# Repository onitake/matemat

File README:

Matemat
=======

The Matemat is a vending machine for carbonated soft drinks.
All hardware and software was designed by members of
(Chaostreff Basel)[1] and released in the form of circuit
diagrams, printed circuit board layouts and source code
for anyone to use and modify.

Under certain restrictions, even commercial exploitation is
permissible. Please see the accompanying LICENSE file for
details.

The name "Matemat" is a portmanteau of "mate" (as in mate
tea) and "automat" (the German word for vending machine).

The device is mainly intended to dispense mate tea based
soft drinks, but may be used for other types of beverages
too.

To build the first prototype, an old vending machine with
a cooled bottle compartment was repurposed.

The software source code can be (downloaded separately)[2].

[1] http://www.chaostreff.ch
[2] https://github.com/onitake/matecontrol

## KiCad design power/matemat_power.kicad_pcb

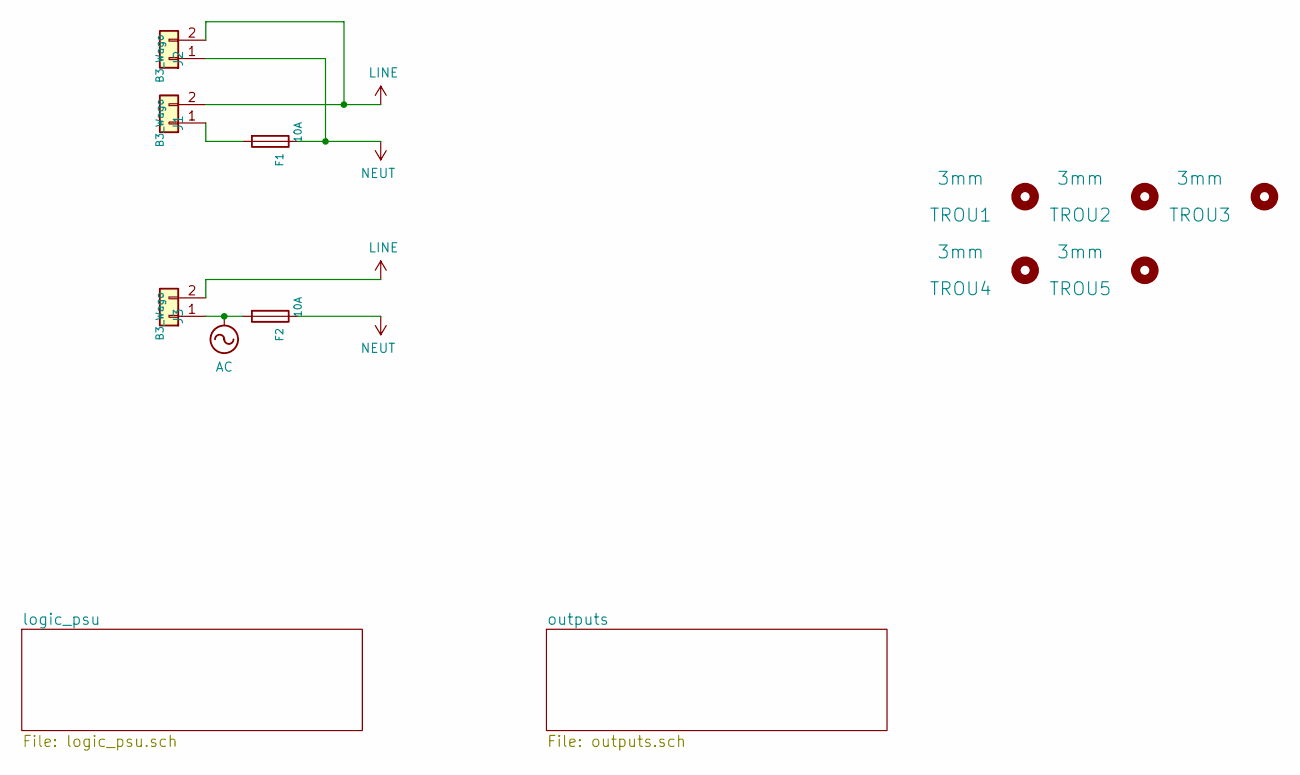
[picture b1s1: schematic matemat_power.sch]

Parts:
F1, F2: 10A; Fuseholder_Cylinder-5x20mm_Schurter_0031_8201_Horizontal_Op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
J1, J2, J3: B3_Wago; TerminalBlock_WAGO_236-402_1x02_P5.00mm_45Degree
TROU1, TROU2, TROU3, TROU4, TROU5: 3mm; MountingHole_3.2mm_M3

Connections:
AC: F2.2, J3.1; also elsewhere on the board
LINE: J1.2, J2.2, J3.2; also elsewhere on the board
NEUT: F1.1, F2.1, J2.1; also elsewhere on the board
unnamed: F1.2, J1.1

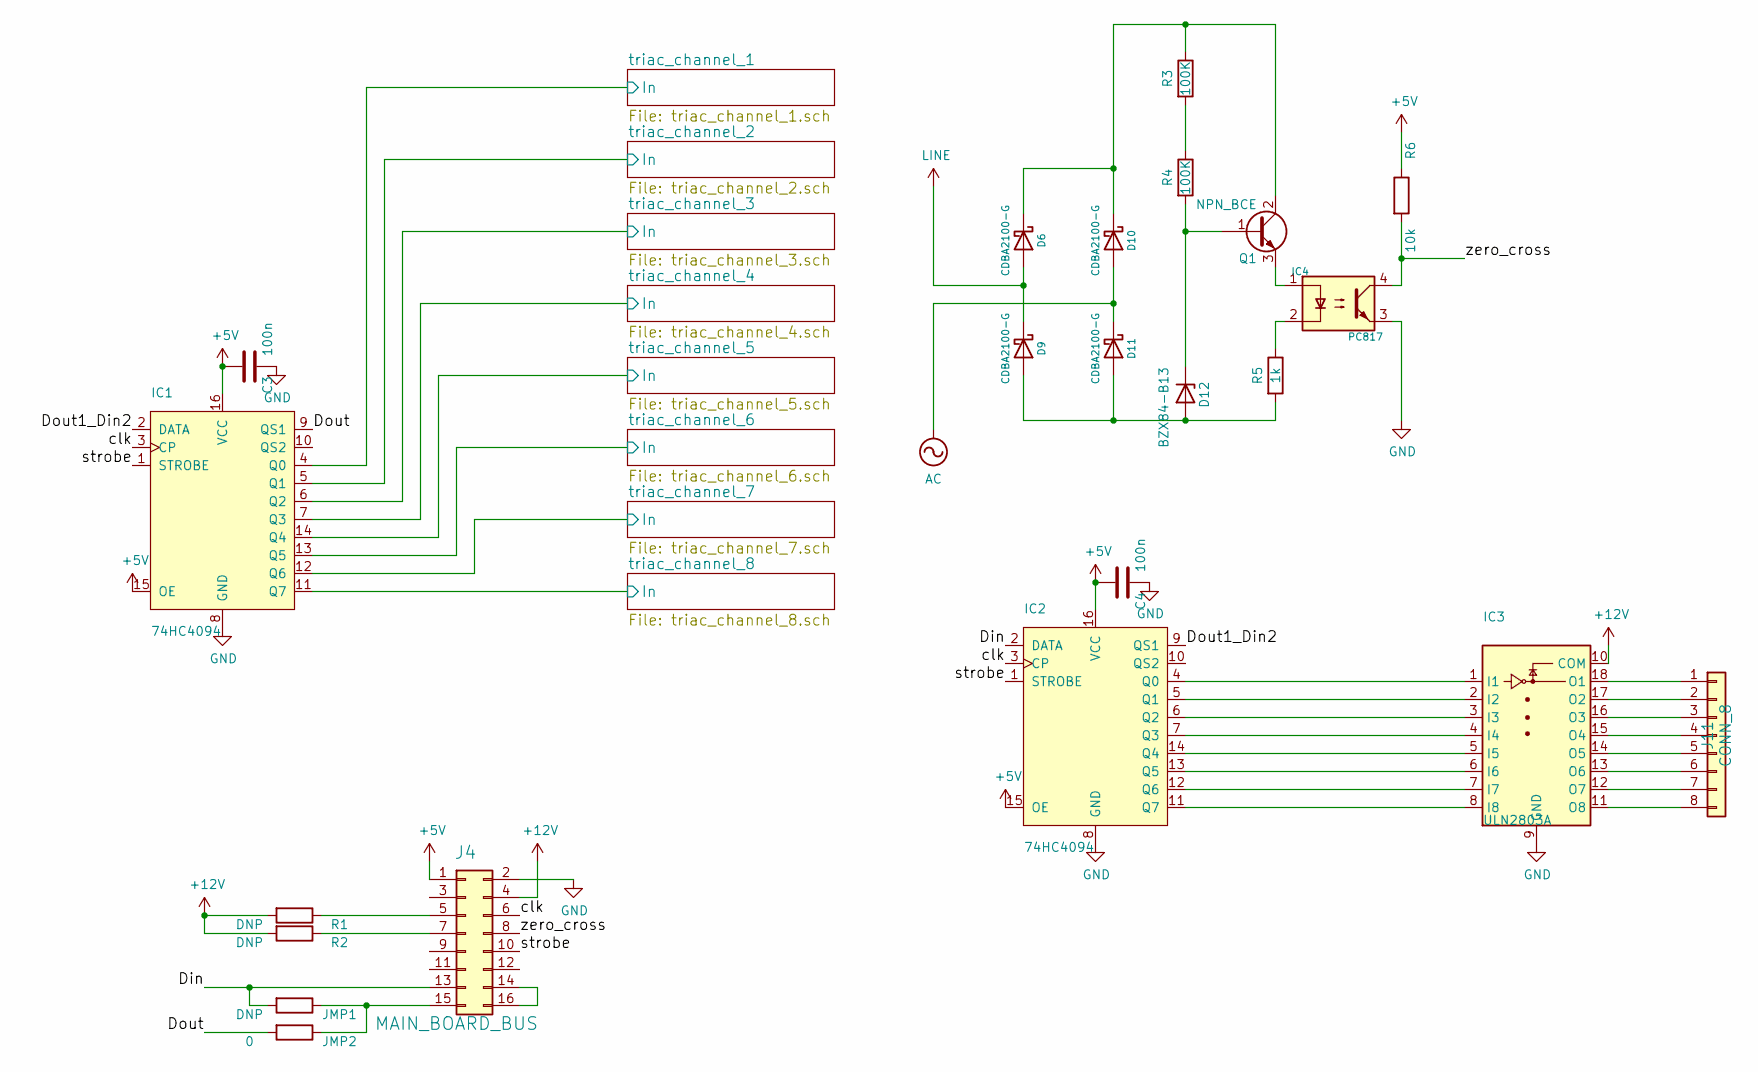
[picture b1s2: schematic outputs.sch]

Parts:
C3, C4: 100n; C_0805_2012Metric_Pad1.18x1.45mm_HandSolder
D6, D9, D10, D11: CDBA2100-G; D_SMA
D12: BZX84-B13; D_SOT-23_ANK
IC1, IC2: 74HC4094; SOIC-16_3.9x9.9mm_P1.27mm
IC3: ULN2803A; SOIC-18W_7.5x11.6mm_P1.27mm
IC4: PC817; DIP-4_W7.62mm
J4: MAIN_BOARD_BUS; PinHeader_2x08_P2.54mm_Vertical
J11: CONN_8; TerminalBlock_Phoenix_MPT-0,5-8-2.54_1x08_P2.54mm_Horizontal
JMP1: DNP; R_0603_1608Metric_Pad0.98x0.95mm_HandSolder
JMP2: 0; R_0603_1608Metric_Pad0.98x0.95mm_HandSolder
Q1: NPN_BCE; TO-220-3_Vertical
R1, R2: DNP; R_0603_1608Metric_Pad0.98x0.95mm_HandSolder
R3, R4: 100K; R_Axial_DIN0309_L9.0mm_D3.2mm_P12.70mm_Horizontal
R5: 1k; R_0805_2012Metric_Pad1.20x1.40mm_HandSolder
R6: 10k; R_0805_2012Metric_Pad1.20x1.40mm_HandSolder

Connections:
+5V: C3.2, C4.2, IC1.15 (OE), IC1.16 (VCC), IC2.15 (OE), IC2.16 (VCC), J4.1, R6.1
+12V: IC3.10 (COM), J4.4, R1.2, R2.2; also elsewhere on the board
/outputs/Din: IC2.2 (DATA), J4.13, JMP1.2
/outputs/Dout: IC1.9 (QS1), JMP2.2
/outputs/Dout1_Din2: IC1.2 (DATA), IC2.9 (QS1)
/outputs/clk: IC1.3 (CP), IC2.3 (CP), J4.6
/outputs/strobe: IC1.1 (STROBE), IC2.1 (STROBE), J4.10
/outputs/triac_channel_1/In: IC1.4 (Q0); also elsewhere on the board
/outputs/triac_channel_2/In: IC1.5 (Q1); also elsewhere on the board
/outputs/triac_channel_3/In: IC1.6 (Q2); also elsewhere on the board
/outputs/triac_channel_4/In: IC1.7 (Q3); also elsewhere on the board
/outputs/triac_channel_5/In: IC1.14 (Q4); also elsewhere on the board
/outputs/triac_channel_6/In: IC1.13 (Q5); also elsewhere on the board
/outputs/triac_channel_7/In: IC1.12 (Q6); also elsewhere on the board
/outputs/triac_channel_8/In: IC1.11 (Q7); also elsewhere on the board
/outputs/zero_cross: IC4.4, J4.8, R6.2
AC: D10.2 (A), D11.1 (K); also elsewhere on the board
GND: C3.1, C4.1, IC1.8 (GND), IC2.8 (GND), IC3.9 (GND), IC4.3, J4.2; also elsewhere on the board
LINE: D6.2 (A), D9.1 (K); also elsewhere on the board
unnamed: D6.1 (K), D10.1 (K), Q1.2 (C), R3.1
unnamed: D9.2 (A), D11.2 (A), D12.2 (A), R5.2
unnamed: D12.1 (K), Q1.1 (B), R4.2
unnamed: IC2.4 (Q0), IC3.1 (I1)
unnamed: IC2.5 (Q1), IC3.2 (I2)
unnamed: IC2.6 (Q2), IC3.3 (I3)
unnamed: IC2.7 (Q3), IC3.4 (I4)
unnamed: IC2.11 (Q7), IC3.8 (I8)
unnamed: IC2.12 (Q6), IC3.7 (I7)
unnamed: IC2.13 (Q5), IC3.6 (I6)
unnamed: IC2.14 (Q4), IC3.5 (I5)
unnamed: IC3.11 (O8), J11.8
unnamed: IC3.12 (O7), J11.7
unnamed: IC3.13 (O6), J11.6
unnamed: IC3.14 (O5), J11.5
unnamed: IC3.15 (O4), J11.4
unnamed: IC3.16 (O3), J11.3
unnamed: IC3.17 (O2), J11.2
unnamed: IC3.18 (O1), J11.1
unnamed: IC4.1, Q1.3 (E)
unnamed: IC4.2, R5.1
unnamed: J4.5, R1.1
unnamed: J4.7, R2.1
unnamed: J4.14, J4.16
unnamed: J4.15, JMP1.1, JMP2.1
unnamed: R3.2, R4.1

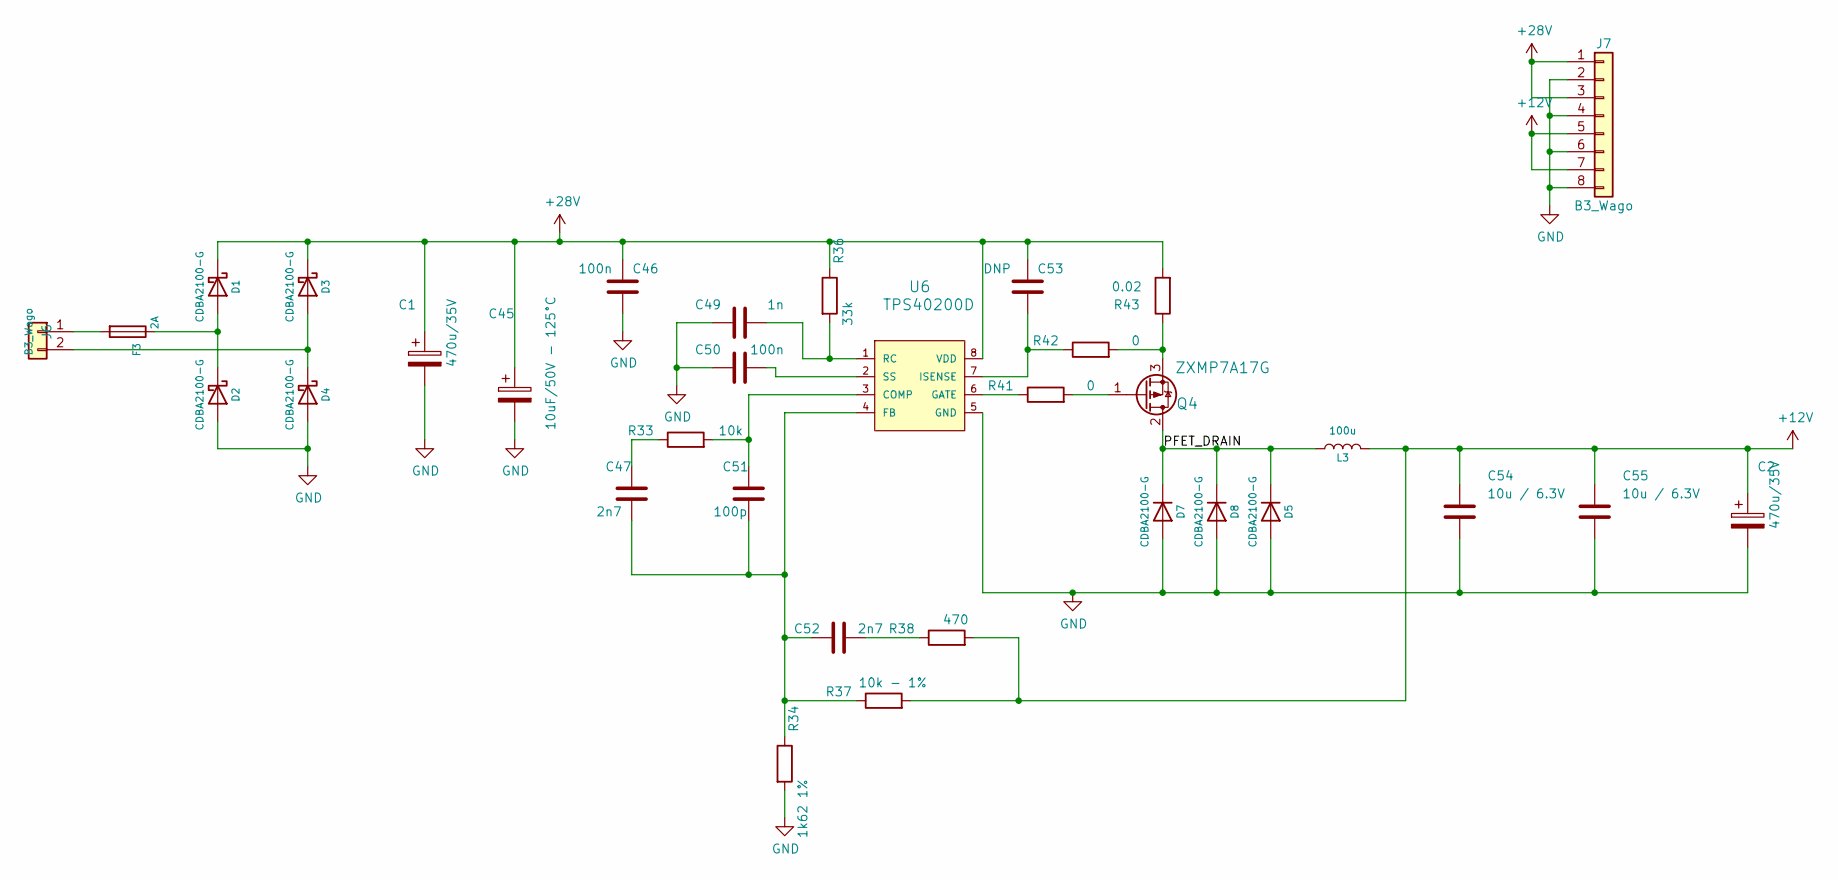
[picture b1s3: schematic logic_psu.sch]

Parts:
C1, C2: 470u/35V; CP_Radial_D10.0mm_P5.00mm
C45: 10uF/50V - 125°C; CP_Radial_D10.0mm_P5.00mm
C46, C50: 100n; C_0805_2012Metric_Pad1.18x1.45mm_HandSolder
C47, C52: 2n7; C_0805_2012Metric_Pad1.18x1.45mm_HandSolder
C49: 1n; C_0805_2012Metric_Pad1.18x1.45mm_HandSolder
C51: 100p; C_0805_2012Metric_Pad1.18x1.45mm_HandSolder
C53: DNP; C_0805_2012Metric_Pad1.18x1.45mm_HandSolder
C54, C55: 10u / 6.3V; C_0805_2012Metric_Pad1.18x1.45mm_HandSolder
D1, D2, D3, D4, D5, D7, D8: CDBA2100-G; D_SMA
F3: 2A; Fuseholder_Cylinder-5x20mm_Schurter_0031_8201_Horizontal_Op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
J6: B3_Wago; TerminalBlock_WAGO_236-402_1x02_P5.00mm_45Degree
J7: B3_Wago; TerminalBlock_WAGO_236-408_1x08_P5.00mm_45Degree
L3: 100u; L_Toroid_Vertical_L22.4mm_W10.2mm_P7.90mm_Vishay_TJ4
Q4: ZXMP7A17G; SOT-223-3_TabPin2
R33: 10k; R_0805_2012Metric_Pad1.20x1.40mm_HandSolder
R34: 1k62 1%; R_0805_2012Metric_Pad1.20x1.40mm_HandSolder
R36: 33k; R_0805_2012Metric_Pad1.20x1.40mm_HandSolder
R37: 10k - 1%; R_0805_2012Metric_Pad1.20x1.40mm_HandSolder
R38: 470; R_0805_2012Metric_Pad1.20x1.40mm_HandSolder
R41, R42: 0; R_0805_2012Metric_Pad1.20x1.40mm_HandSolder
R43: 0.02; R_2010_5025Metric_Pad1.40x2.65mm_HandSolder
U6: TPS40200D; SOIC-8_3.9x4.9mm_P1.27mm

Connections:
+12V: C2.1, C54.1, C55.1, J7.5, J7.7, L3.2, R37.2, R38.2; also elsewhere on the board
+28V: C1.1, C45.1, C46.1, C53.1, D1.1 (K), D3.1 (K), J7.1, J7.3, R36.1, R43.2, U6.8 (VDD)
/logic_psu/PFET_DRAIN: D5.1 (K), D7.1 (K), D8.1 (K), L3.1, Q4.2 (D)
GND: C1.2, C2.2, C45.2, C46.2, C49.1, C50.1, C54.2, C55.2, D2.2 (A), D4.2 (A), D5.2 (A), D7.2 (A), D8.2 (A), J7.2, J7.4, J7.6, J7.8, R34.2, U6.5 (GND); also elsewhere on the board
unnamed: C47.1, R33.1
unnamed: C47.2, C51.2, C52.1, R34.1, R37.1, U6.4 (FB)
unnamed: C49.2, R36.2, U6.1 (RC)
unnamed: C50.2, U6.2 (SS)
unnamed: C51.1, R33.2, U6.3 (COMP)
unnamed: C52.2, R38.1
unnamed: C53.2, R42.1, U6.7 (ISENSE)
unnamed: D1.2 (A), D2.1 (K), F3.1
unnamed: D3.2 (A), D4.1 (K), J6.2
unnamed: F3.2, J6.1
unnamed: Q4.1 (G), R41.2
unnamed: Q4.3 (S), R42.2, R43.1
unnamed: R41.1, U6.6 (GATE)

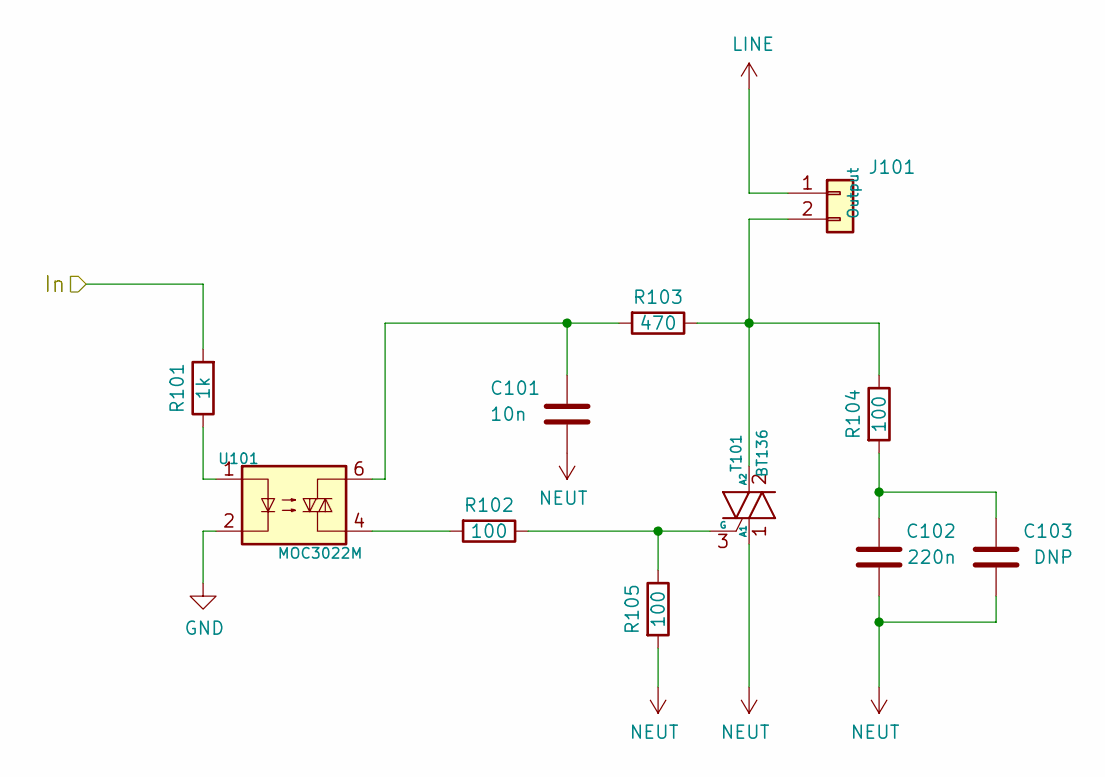
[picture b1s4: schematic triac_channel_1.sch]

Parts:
C101: 10n; C_Rect_L7.0mm_W2.5mm_P5.00mm
C102: 220n; C_Rect_L18.0mm_W5.0mm_P15.00mm_FKS3_FKP3
C103: DNP; C_Rect_L13.0mm_W4.0mm_P10.00mm_FKS3_FKP3_MKS4
J101: Output; TerminalBlock_WAGO_236-402_1x02_P5.00mm_45Degree
R101: 1k; R_0805_2012Metric_Pad1.20x1.40mm_HandSolder
R102, R104: 100; R_Axial_DIN0309_L9.0mm_D3.2mm_P12.70mm_Horizontal
R103: 470; R_Axial_DIN0309_L9.0mm_D3.2mm_P12.70mm_Horizontal
R105: 100; R_0805_2012Metric_Pad1.20x1.40mm_HandSolder
T101: BT136; TO-220-3_Vertical
U101: MOC3022M; DIP-6_W7.62mm_LongPads

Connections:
/outputs/triac_channel_1/In: R101.2; also elsewhere on the board
GND: U101.2; also elsewhere on the board
LINE: J101.1; also elsewhere on the board
NEUT: C101.2, C102.2, C103.2, R105.2, T101.1 (A1); also elsewhere on the board
unnamed: C101.1, R103.2, U101.6
unnamed: C102.1, C103.1, R104.2
unnamed: J101.2, R103.1, R104.1, T101.2 (A2)
unnamed: R101.1, U101.1
unnamed: R102.1, R105.1, T101.3 (G)
unnamed: R102.2, U101.4

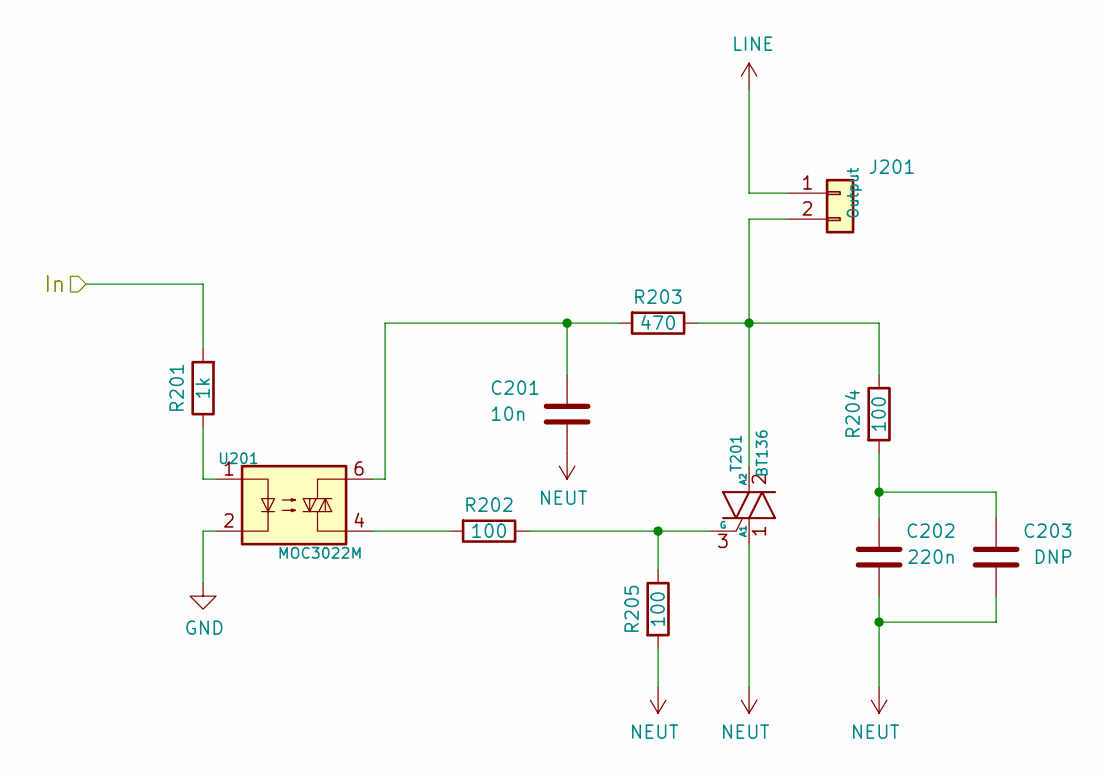
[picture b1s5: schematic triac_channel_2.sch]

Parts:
C201: 10n; C_Rect_L7.0mm_W2.5mm_P5.00mm
C202: 220n; C_Rect_L18.0mm_W5.0mm_P15.00mm_FKS3_FKP3
C203: DNP; C_Rect_L13.0mm_W4.0mm_P10.00mm_FKS3_FKP3_MKS4
J201: Output; TerminalBlock_WAGO_236-402_1x02_P5.00mm_45Degree
R201: 1k; R_0805_2012Metric_Pad1.20x1.40mm_HandSolder
R202, R204: 100; R_Axial_DIN0309_L9.0mm_D3.2mm_P12.70mm_Horizontal
R203: 470; R_Axial_DIN0309_L9.0mm_D3.2mm_P12.70mm_Horizontal
R205: 100; R_0805_2012Metric_Pad1.20x1.40mm_HandSolder
T201: BT136; TO-220-3_Vertical
U201: MOC3022M; DIP-6_W7.62mm_LongPads

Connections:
/outputs/triac_channel_2/In: R201.2; also elsewhere on the board
GND: U201.2; also elsewhere on the board
LINE: J201.1; also elsewhere on the board
NEUT: C201.2, C202.2, C203.2, R205.2, T201.1 (A1); also elsewhere on the board
unnamed: C201.1, R203.2, U201.6
unnamed: C202.1, C203.1, R204.2
unnamed: J201.2, R203.1, R204.1, T201.2 (A2)
unnamed: R201.1, U201.1
unnamed: R202.1, R205.1, T201.3 (G)
unnamed: R202.2, U201.4

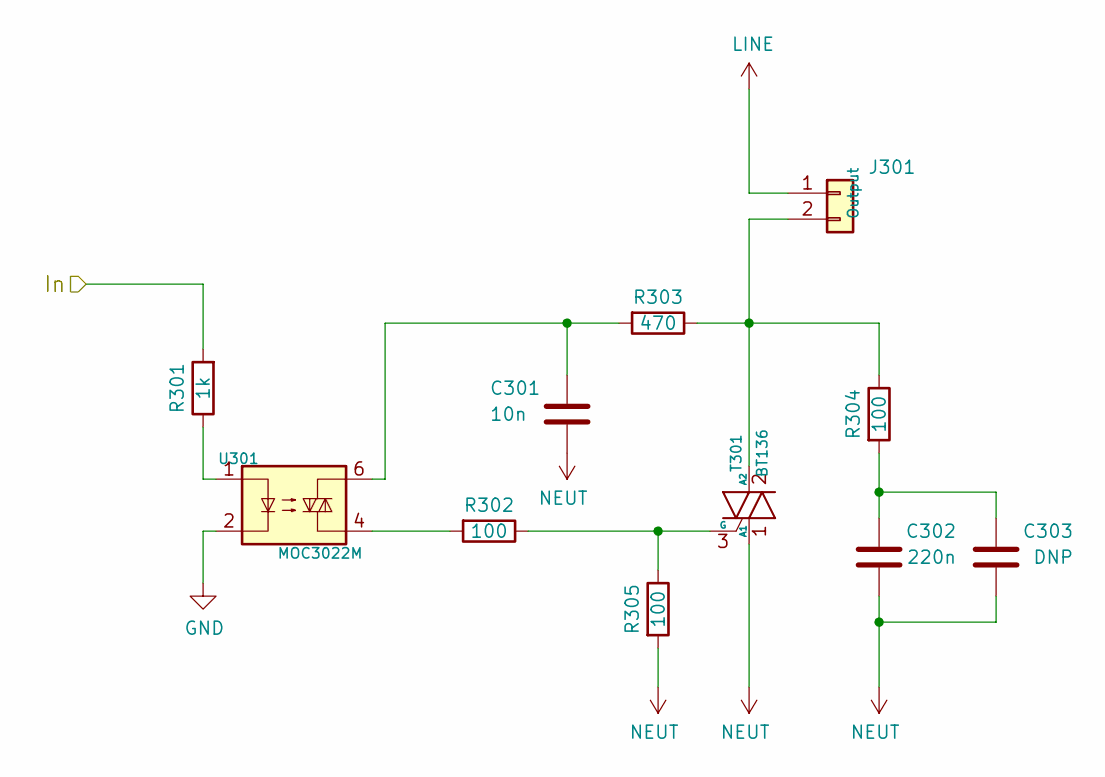
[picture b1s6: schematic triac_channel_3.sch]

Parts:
C301: 10n; C_Rect_L7.0mm_W2.5mm_P5.00mm
C302: 220n; C_Rect_L18.0mm_W5.0mm_P15.00mm_FKS3_FKP3
C303: DNP; C_Rect_L13.0mm_W4.0mm_P10.00mm_FKS3_FKP3_MKS4
J301: Output; TerminalBlock_WAGO_236-402_1x02_P5.00mm_45Degree
R301: 1k; R_0805_2012Metric_Pad1.20x1.40mm_HandSolder
R302, R304: 100; R_Axial_DIN0309_L9.0mm_D3.2mm_P12.70mm_Horizontal
R303: 470; R_Axial_DIN0309_L9.0mm_D3.2mm_P12.70mm_Horizontal
R305: 100; R_0805_2012Metric_Pad1.20x1.40mm_HandSolder
T301: BT136; TO-220-3_Vertical
U301: MOC3022M; DIP-6_W7.62mm_LongPads

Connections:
/outputs/triac_channel_3/In: R301.2; also elsewhere on the board
GND: U301.2; also elsewhere on the board
LINE: J301.1; also elsewhere on the board
NEUT: C301.2, C302.2, C303.2, R305.2, T301.1 (A1); also elsewhere on the board
unnamed: C301.1, R303.2, U301.6
unnamed: C302.1, C303.1, R304.2
unnamed: J301.2, R303.1, R304.1, T301.2 (A2)
unnamed: R301.1, U301.1
unnamed: R302.1, R305.1, T301.3 (G)
unnamed: R302.2, U301.4

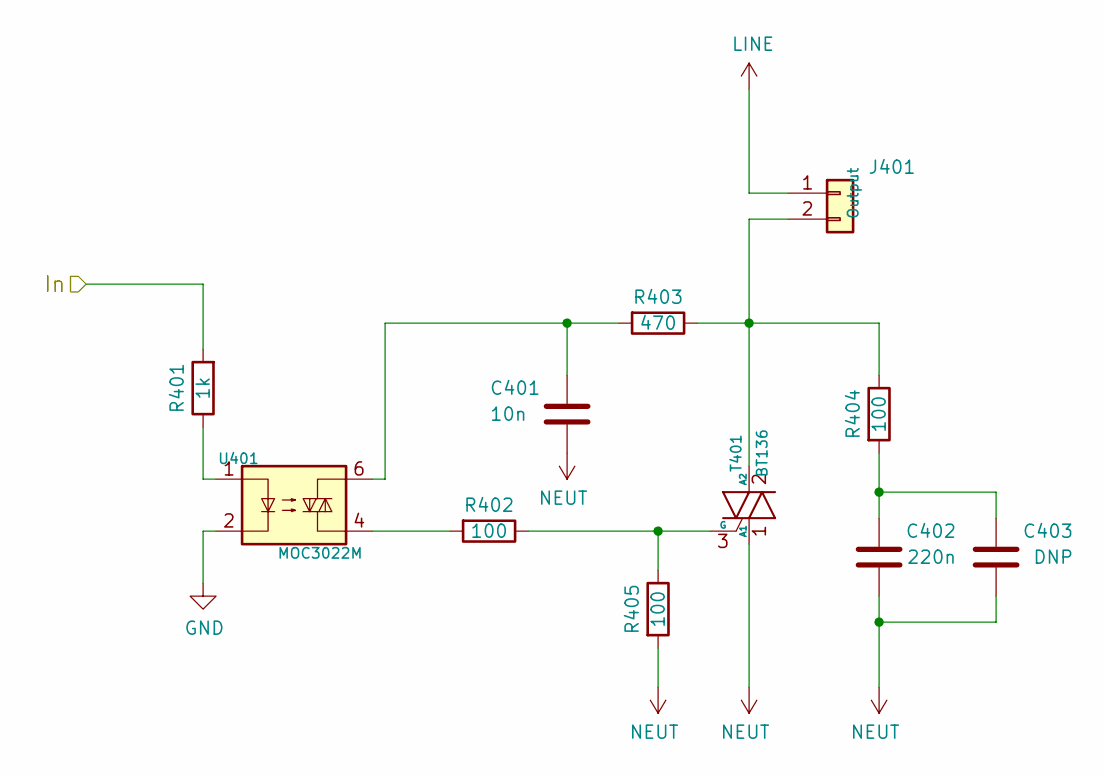
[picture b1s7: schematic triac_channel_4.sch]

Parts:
C401: 10n; C_Rect_L7.0mm_W2.5mm_P5.00mm
C402: 220n; C_Rect_L18.0mm_W5.0mm_P15.00mm_FKS3_FKP3
C403: DNP; C_Rect_L13.0mm_W4.0mm_P10.00mm_FKS3_FKP3_MKS4
J401: Output; TerminalBlock_WAGO_236-402_1x02_P5.00mm_45Degree
R401: 1k; R_0805_2012Metric_Pad1.20x1.40mm_HandSolder
R402, R404: 100; R_Axial_DIN0309_L9.0mm_D3.2mm_P12.70mm_Horizontal
R403: 470; R_Axial_DIN0309_L9.0mm_D3.2mm_P12.70mm_Horizontal
R405: 100; R_0805_2012Metric_Pad1.20x1.40mm_HandSolder
T401: BT136; TO-220-3_Vertical
U401: MOC3022M; DIP-6_W7.62mm_LongPads

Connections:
/outputs/triac_channel_4/In: R401.2; also elsewhere on the board
GND: U401.2; also elsewhere on the board
LINE: J401.1; also elsewhere on the board
NEUT: C401.2, C402.2, C403.2, R405.2, T401.1 (A1); also elsewhere on the board
unnamed: C401.1, R403.2, U401.6
unnamed: C402.1, C403.1, R404.2
unnamed: J401.2, R403.1, R404.1, T401.2 (A2)
unnamed: R401.1, U401.1
unnamed: R402.1, R405.1, T401.3 (G)
unnamed: R402.2, U401.4

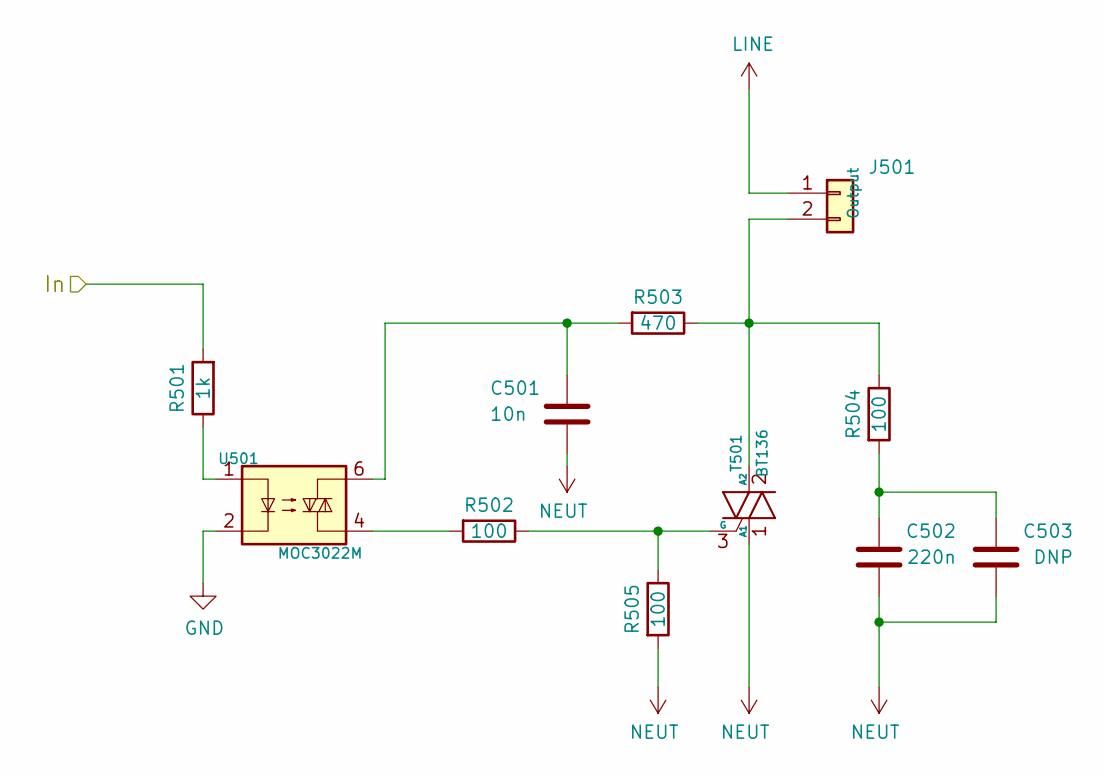
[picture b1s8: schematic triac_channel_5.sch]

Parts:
C501: 10n; C_Rect_L7.0mm_W2.5mm_P5.00mm
C502: 220n; C_Rect_L18.0mm_W5.0mm_P15.00mm_FKS3_FKP3
C503: DNP; C_Rect_L13.0mm_W4.0mm_P10.00mm_FKS3_FKP3_MKS4
J501: Output; TerminalBlock_WAGO_236-402_1x02_P5.00mm_45Degree
R501: 1k; R_0805_2012Metric_Pad1.20x1.40mm_HandSolder
R502, R504: 100; R_Axial_DIN0309_L9.0mm_D3.2mm_P12.70mm_Horizontal
R503: 470; R_Axial_DIN0309_L9.0mm_D3.2mm_P12.70mm_Horizontal
R505: 100; R_0805_2012Metric_Pad1.20x1.40mm_HandSolder
T501: BT136; TO-220-3_Vertical
U501: MOC3022M; DIP-6_W7.62mm_LongPads

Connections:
/outputs/triac_channel_5/In: R501.2; also elsewhere on the board
GND: U501.2; also elsewhere on the board
LINE: J501.1; also elsewhere on the board
NEUT: C501.2, C502.2, C503.2, R505.2, T501.1 (A1); also elsewhere on the board
unnamed: C501.1, R503.2, U501.6
unnamed: C502.1, C503.1, R504.2
unnamed: J501.2, R503.1, R504.1, T501.2 (A2)
unnamed: R501.1, U501.1
unnamed: R502.1, R505.1, T501.3 (G)
unnamed: R502.2, U501.4

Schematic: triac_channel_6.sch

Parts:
C601: 10n; C_Rect_L7.0mm_W2.5mm_P5.00mm
C602: 220n; C_Rect_L18.0mm_W5.0mm_P15.00mm_FKS3_FKP3
C603: DNP; C_Rect_L13.0mm_W4.0mm_P10.00mm_FKS3_FKP3_MKS4
J601: Output; TerminalBlock_WAGO_236-402_1x02_P5.00mm_45Degree
R601: 1k; R_0805_2012Metric_Pad1.20x1.40mm_HandSolder
R602, R604: 100; R_Axial_DIN0309_L9.0mm_D3.2mm_P12.70mm_Horizontal
R603: 470; R_Axial_DIN0309_L9.0mm_D3.2mm_P12.70mm_Horizontal
R605: 100; R_0805_2012Metric_Pad1.20x1.40mm_HandSolder
T601: BT136; TO-220-3_Vertical
U601: MOC3022M; DIP-6_W7.62mm_LongPads

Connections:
/outputs/triac_channel_6/In: R601.2; also elsewhere on the board
GND: U601.2; also elsewhere on the board
LINE: J601.1; also elsewhere on the board
NEUT: C601.2, C602.2, C603.2, R605.2, T601.1 (A1); also elsewhere on the board
unnamed: C601.1, R603.2, U601.6
unnamed: C602.1, C603.1, R604.2
unnamed: J601.2, R603.1, R604.1, T601.2 (A2)
unnamed: R601.1, U601.1
unnamed: R602.1, R605.1, T601.3 (G)
unnamed: R602.2, U601.4

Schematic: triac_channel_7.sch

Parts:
C701: 10n; C_Rect_L7.0mm_W2.5mm_P5.00mm
C702: 220n; C_Rect_L18.0mm_W5.0mm_P15.00mm_FKS3_FKP3
C703: DNP; C_Rect_L13.0mm_W4.0mm_P10.00mm_FKS3_FKP3_MKS4
J701: Output; TerminalBlock_WAGO_236-402_1x02_P5.00mm_45Degree
R701: 1k; R_0805_2012Metric_Pad1.20x1.40mm_HandSolder
R702, R704: 100; R_Axial_DIN0309_L9.0mm_D3.2mm_P12.70mm_Horizontal
R703: 470; R_Axial_DIN0309_L9.0mm_D3.2mm_P12.70mm_Horizontal
R705: 100; R_0805_2012Metric_Pad1.20x1.40mm_HandSolder
T701: BT136; TO-220-3_Vertical
U701: MOC3022M; DIP-6_W7.62mm_LongPads

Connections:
/outputs/triac_channel_7/In: R701.2; also elsewhere on the board
GND: U701.2; also elsewhere on the board
LINE: J701.1; also elsewhere on the board
NEUT: C701.2, C702.2, C703.2, R705.2, T701.1 (A1); also elsewhere on the board
unnamed: C701.1, R703.2, U701.6
unnamed: C702.1, C703.1, R704.2
unnamed: J701.2, R703.1, R704.1, T701.2 (A2)
unnamed: R701.1, U701.1
unnamed: R702.1, R705.1, T701.3 (G)
unnamed: R702.2, U701.4

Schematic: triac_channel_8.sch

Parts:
C801: 10n; C_Rect_L7.0mm_W2.5mm_P5.00mm
C802: 220n; C_Rect_L18.0mm_W5.0mm_P15.00mm_FKS3_FKP3
C803: DNP; C_Rect_L13.0mm_W4.0mm_P10.00mm_FKS3_FKP3_MKS4
J801: Output; TerminalBlock_WAGO_236-402_1x02_P5.00mm_45Degree
R801: 1k; R_0805_2012Metric_Pad1.20x1.40mm_HandSolder
R802, R804: 100; R_Axial_DIN0309_L9.0mm_D3.2mm_P12.70mm_Horizontal
R803: 470; R_Axial_DIN0309_L9.0mm_D3.2mm_P12.70mm_Horizontal
R805: 100; R_0805_2012Metric_Pad1.20x1.40mm_HandSolder
T801: BT136; TO-220-3_Vertical
U801: MOC3022M; DIP-6_W7.62mm_LongPads

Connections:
/outputs/triac_channel_8/In: R801.2; also elsewhere on the board
GND: U801.2; also elsewhere on the board
LINE: J801.1; also elsewhere on the board
NEUT: C801.2, C802.2, C803.2, R805.2, T801.1 (A1); also elsewhere on the board
unnamed: C801.1, R803.2, U801.6
unnamed: C802.1, C803.1, R804.2
unnamed: J801.2, R803.1, R804.1, T801.2 (A2)
unnamed: R801.1, U801.1
unnamed: R802.1, R805.1, T801.3 (G)
unnamed: R802.2, U801.4

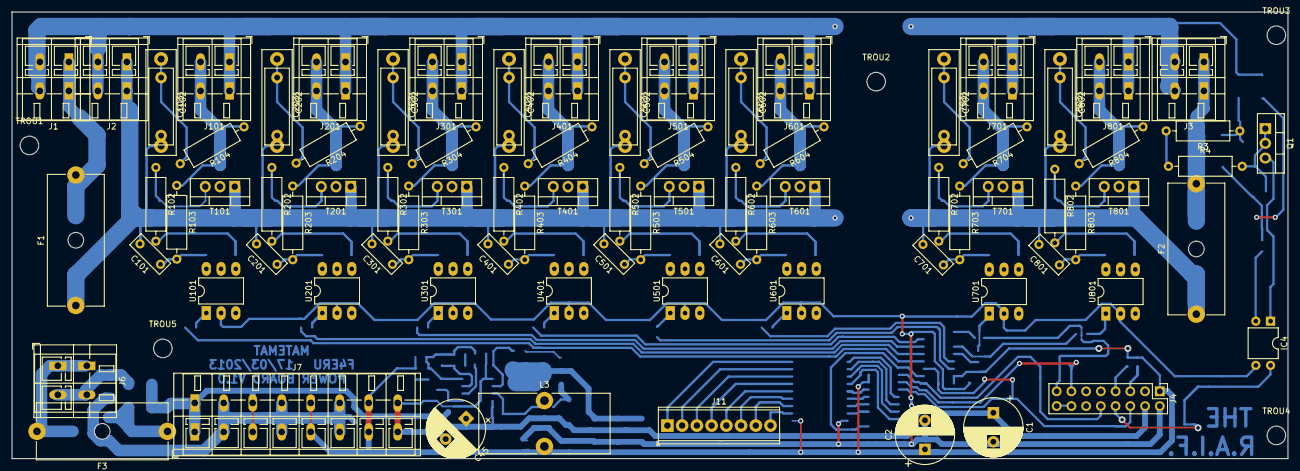
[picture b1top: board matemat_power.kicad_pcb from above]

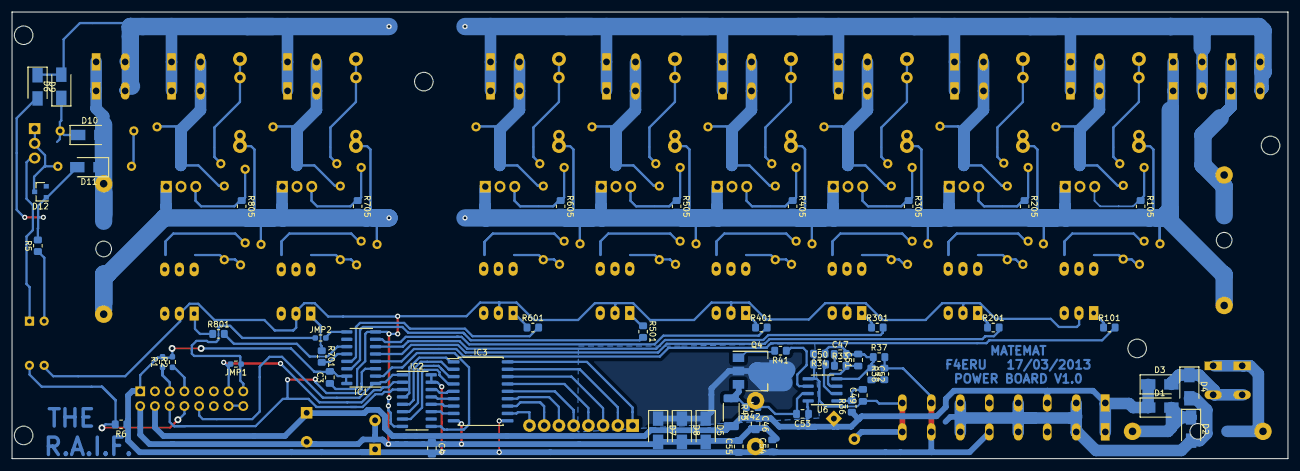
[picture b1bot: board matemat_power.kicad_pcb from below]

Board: 2 copper layers, 220.0 x 77.0 mm, 153 parts (58 on the bottom side), 110 nets.

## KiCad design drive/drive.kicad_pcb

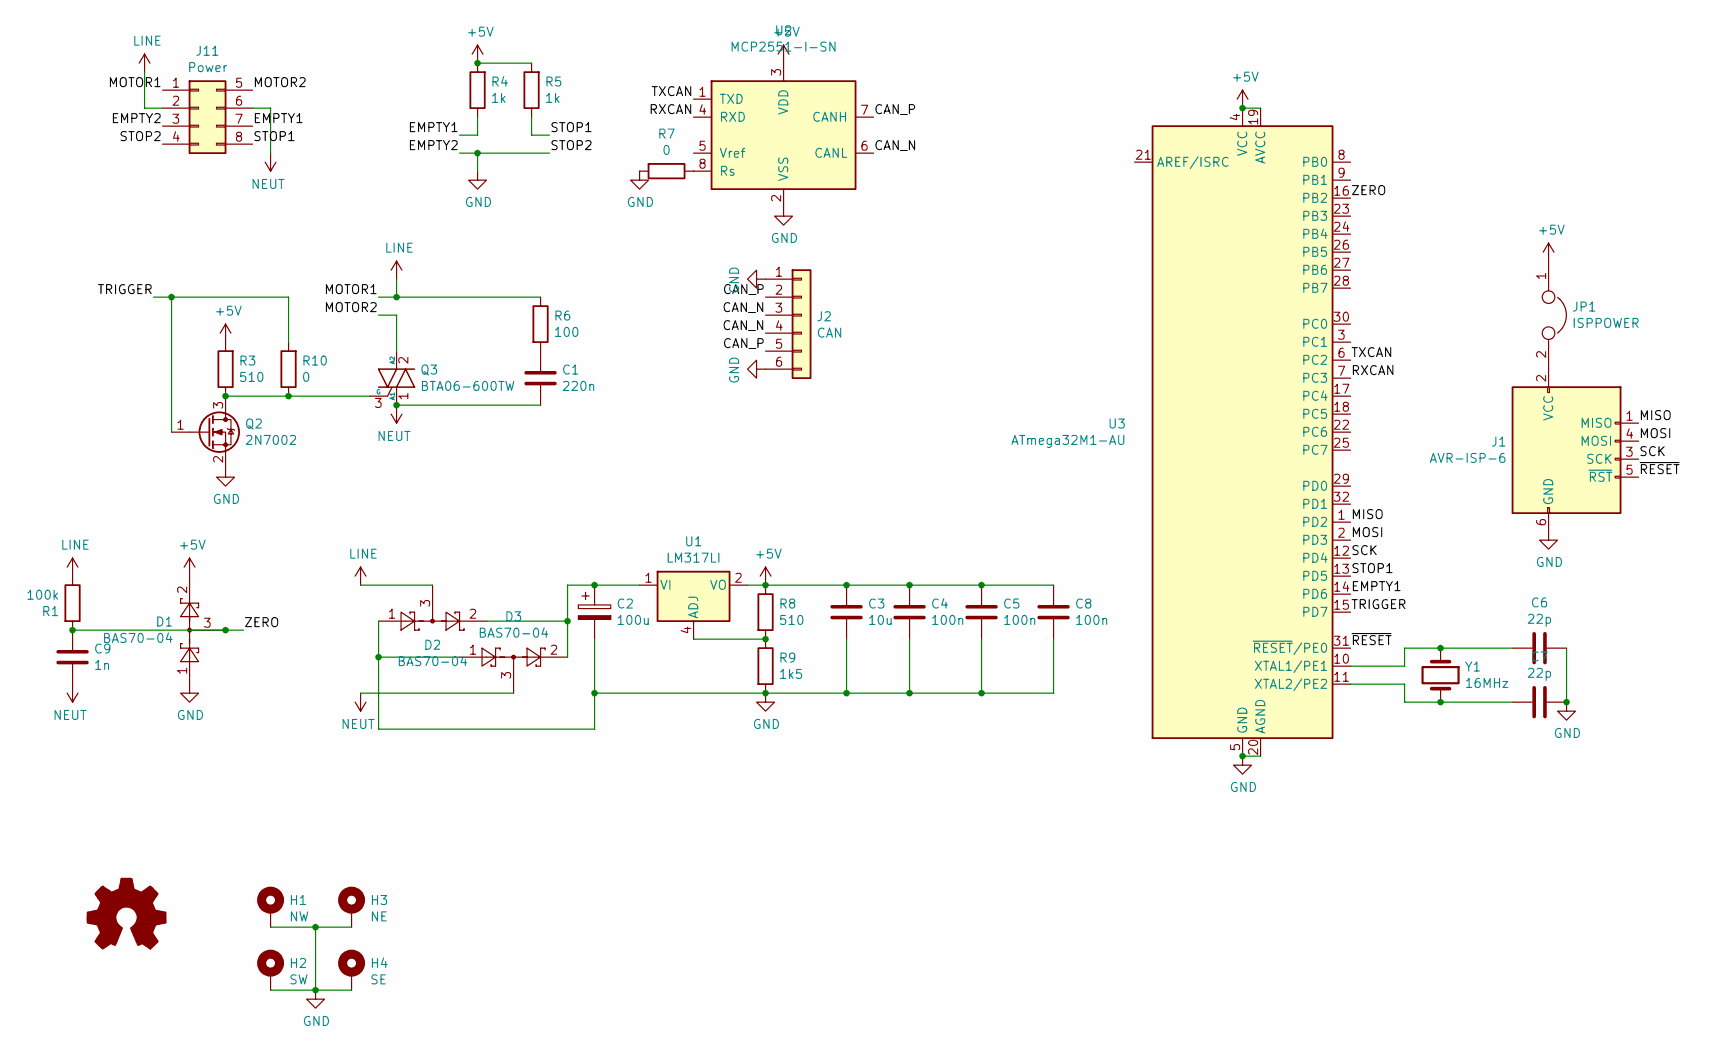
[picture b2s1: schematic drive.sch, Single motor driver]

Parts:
C1: 220n; C_Rect_L7.2mm_W2.5mm_P5.00mm_FKS2_FKP2_MKS2_MKP2
C2: 100u; CP_Radial_D8.0mm_P3.50mm
C3: 10u; C_0805_2012Metric_Pad1.15x1.40mm_HandSolder
C4, C5, C8: 100n; C_0805_2012Metric_Pad1.15x1.40mm_HandSolder
C6, C7: 22p; C_0805_2012Metric_Pad1.15x1.40mm_HandSolder
C9: 1n; C_0805_2012Metric_Pad1.15x1.40mm_HandSolder
D1, D2, D3: BAS70-04; SOT-23
H1: NW; MountingHole_3.2mm_M3_ISO7380_Pad
H2: SW; MountingHole_3.2mm_M3_ISO7380_Pad
H3: NE; MountingHole_3.2mm_M3_ISO7380_Pad
H4: SE; MountingHole_3.2mm_M3_ISO7380_Pad
J1: AVR-ISP-6; PinHeader_2x03_P2.54mm_Vertical
J2: CAN; TerminalBlock_TE_282834-6_1x06_P2.54mm_Horizontal
J11: Power; Molex_Mini-Fit_Jr_5569-08A2_2x04_P4.20mm_Horizontal
JP1: ISPPOWER; PinHeader_1x02_P2.54mm_Vertical
Q2: 2N7002; SOT-23
Q3: BTA06-600TW; TO-220-3_Vertical
R1: 100k; R_0805_2012Metric_Pad1.15x1.40mm_HandSolder
R3, R8: 510; R_0805_2012Metric_Pad1.15x1.40mm_HandSolder
R4, R5: 1k; R_0805_2012Metric_Pad1.15x1.40mm_HandSolder
R6: 100; R_Axial_DIN0207_L6.3mm_D2.5mm_P7.62mm_Horizontal
R7, R10: 0; R_0805_2012Metric_Pad1.15x1.40mm_HandSolder
R9: 1k5; R_0805_2012Metric_Pad1.15x1.40mm_HandSolder
U1: LM317LI; SOIC-8_3.9x4.9mm_P1.27mm
U2: MCP2551-I-SN; SOIC-8_3.9x4.9mm_P1.27mm
U3: ATmega32M1-AU; TQFP-32_7x7mm_P0.8mm
Y1: 16MHz; Crystal_SMD_HC49-SD

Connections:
+5V: C3.1, C4.1, C5.1, C8.1, D1.2, JP1.1, R3.2, R4.2, R5.2, R8.1, U1.2 (VO), U1.3 (VO), U1.6 (VO), U1.7 (VO), U2.3 (VDD), U3.4 (VCC), U3.19 (AVCC)
/CAN_N: J2.3, J2.4, U2.6 (CANL)
/CAN_P: J2.2, J2.5, U2.7 (CANH)
/EMPTY1: J11.7, R4.1, U3.14 (PD6)
/MISO: J1.1 (MISO), U3.1 (PD2)
/MOSI: J1.4 (MOSI), U3.2 (PD3)
/MOTOR2: J11.5, Q3.2 (A2)
/RXCAN: U2.4 (RXD), U3.7 (PC3)
/SCK: J1.3 (SCK), U3.12 (PD4)
/STOP1: J11.8, R5.1, U3.13 (PD5)
/TRIGGER: Q2.1 (G), R10.2, U3.15 (PD7)
/TXCAN: U2.1 (TXD), U3.6 (PC2)
/ZERO: C9.1, D1.3, R1.2, U3.16 (PB2)
/~RESET: J1.5 (~RST), U3.31 (~RESET~/PE0)
GND: C2.2, C3.2, C4.2, C5.2, C6.1, C7.1, C8.2, D1.1, D2.1, D3.1, H1.1, H2.1, H3.1, H4.1, J1.6 (GND), J2.1, J2.6, J11.3, J11.4, Q2.2 (S), R7.2, R9.2, U2.2 (VSS), U3.5 (GND), U3.20 (AGND)
LINE: D2.3, J11.1, J11.2, R1.1, R6.1
NEUT: C1.2, C9.2, D3.3, J11.6, Q3.1 (A1)
unnamed: C1.1, R6.2
unnamed: C2.1, D2.2, D3.2, U1.1 (VI)
unnamed: C6.2, U3.10 (XTAL1/PE1), Y1.1
unnamed: C7.2, U3.11 (XTAL2/PE2), Y1.2
unnamed: J1.2 (VCC), JP1.2
unnamed: Q2.3 (D), Q3.3 (G), R3.1, R10.1
unnamed: R7.1, U2.8 (Rs)
unnamed: R8.2, R9.1, U1.4 (ADJ)

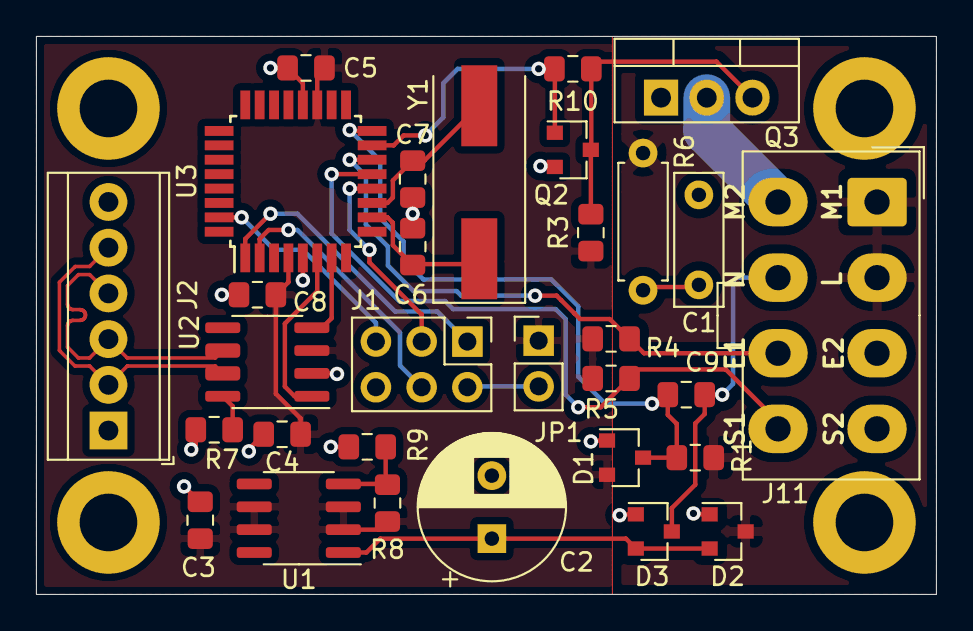
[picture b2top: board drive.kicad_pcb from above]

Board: 2 copper layers, 50.0 x 31.0 mm, 35 parts (0 on the bottom side), 25 nets.

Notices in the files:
control.sch:
Copyright (c) 2015 Gregor Riepl
control/control.kicad_pcb:
© 2015 Chaostreff Basel
